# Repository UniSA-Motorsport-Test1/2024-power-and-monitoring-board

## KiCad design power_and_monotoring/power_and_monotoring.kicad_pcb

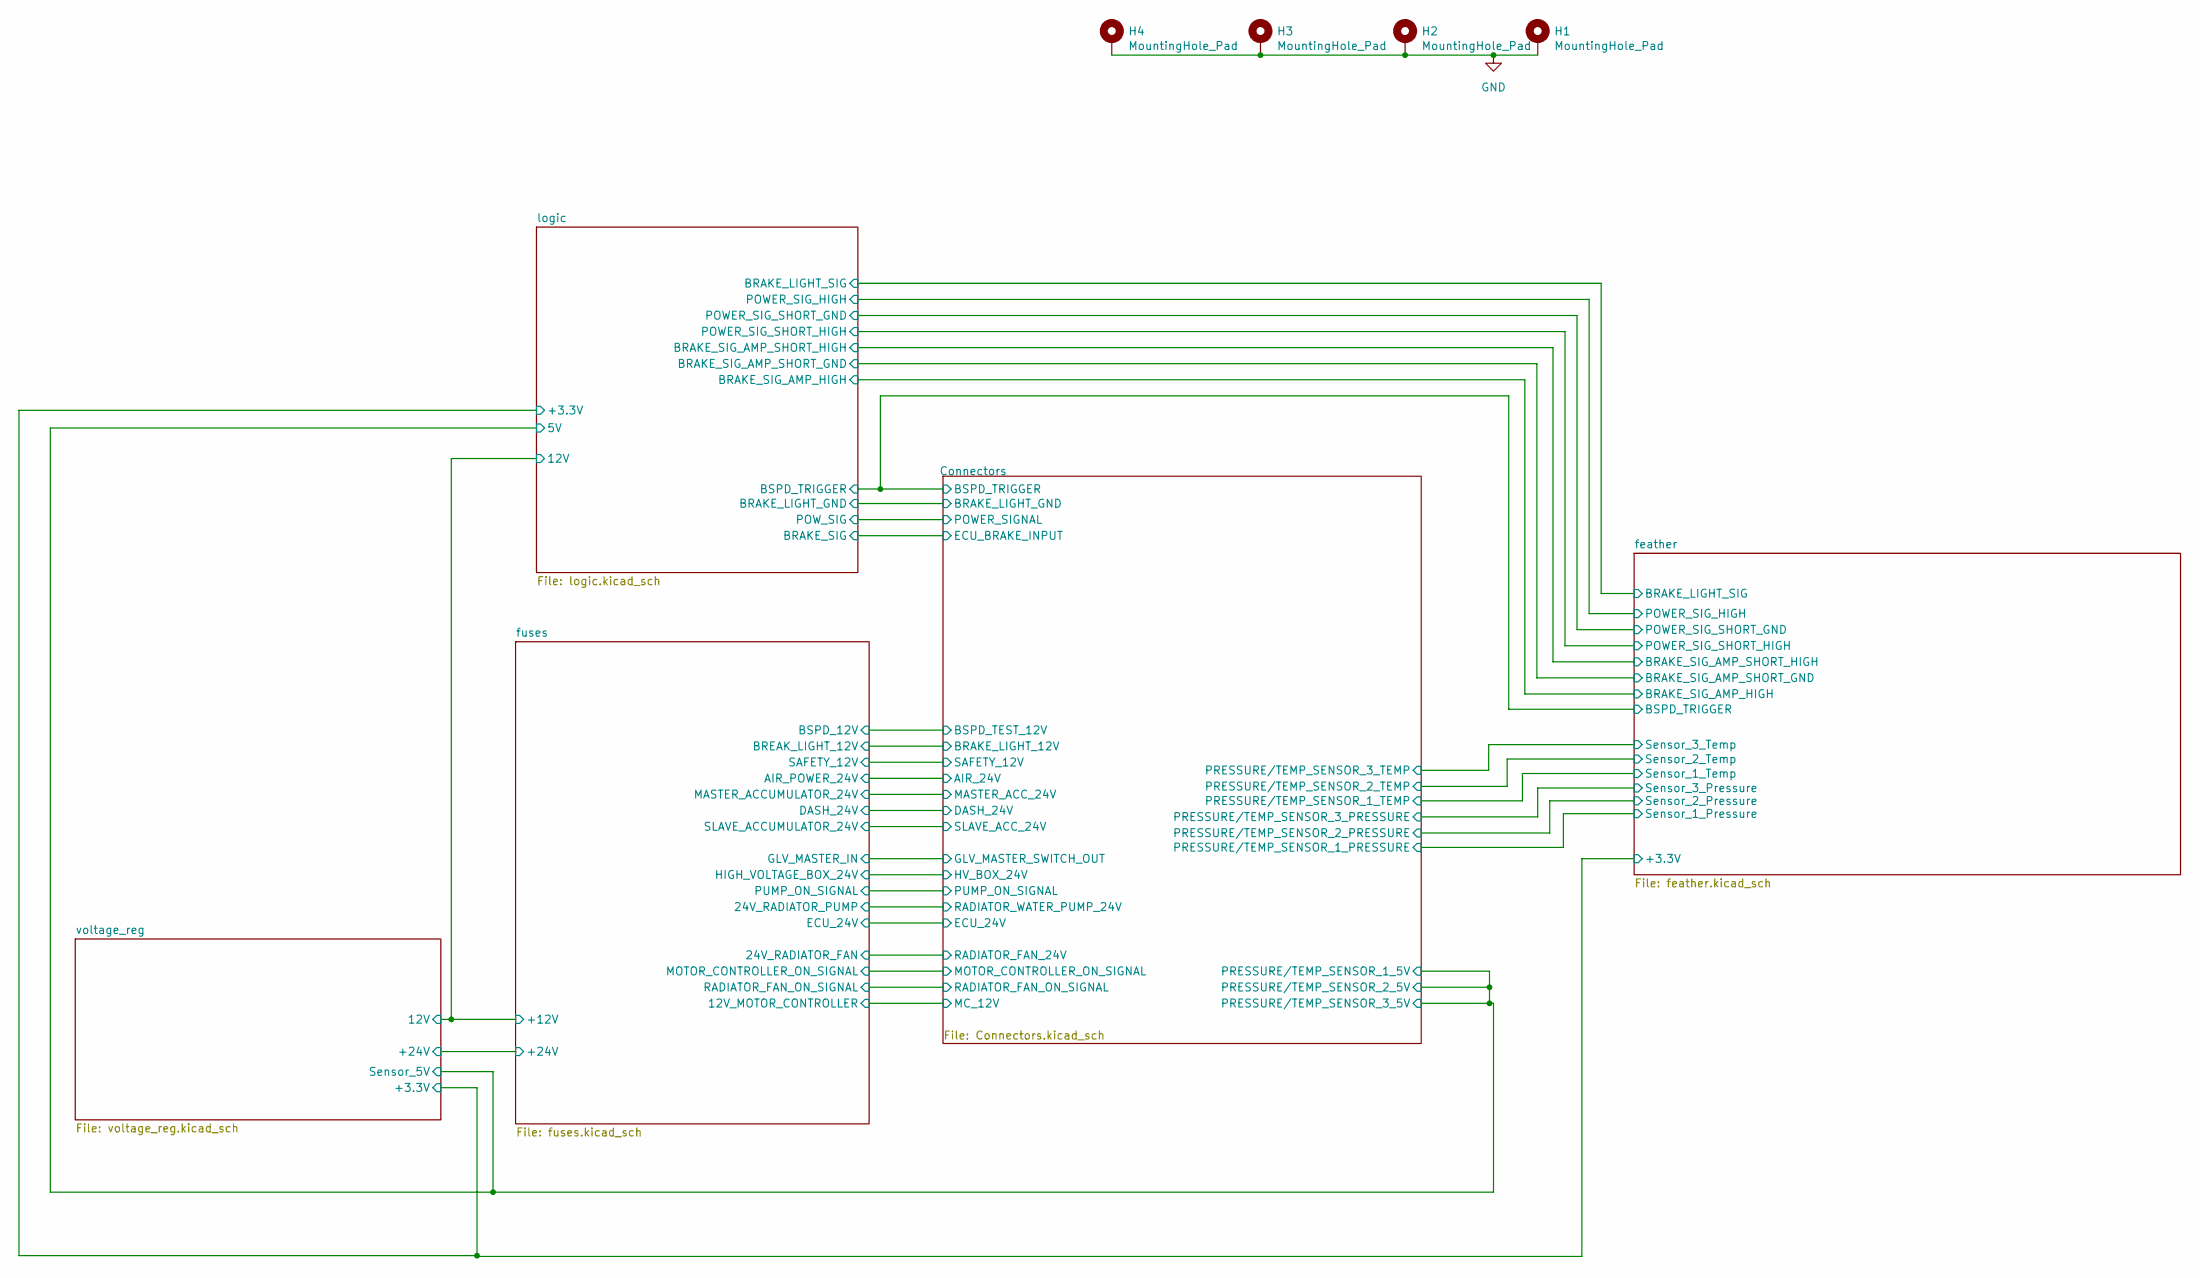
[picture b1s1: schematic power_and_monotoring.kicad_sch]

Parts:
H1, H2, H3, H4: MountingHole_Pad; MountingHole_3.2mm_M3_Pad_Via

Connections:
GND: H1.1, H2.1, H3.1, H4.1; also elsewhere on the board

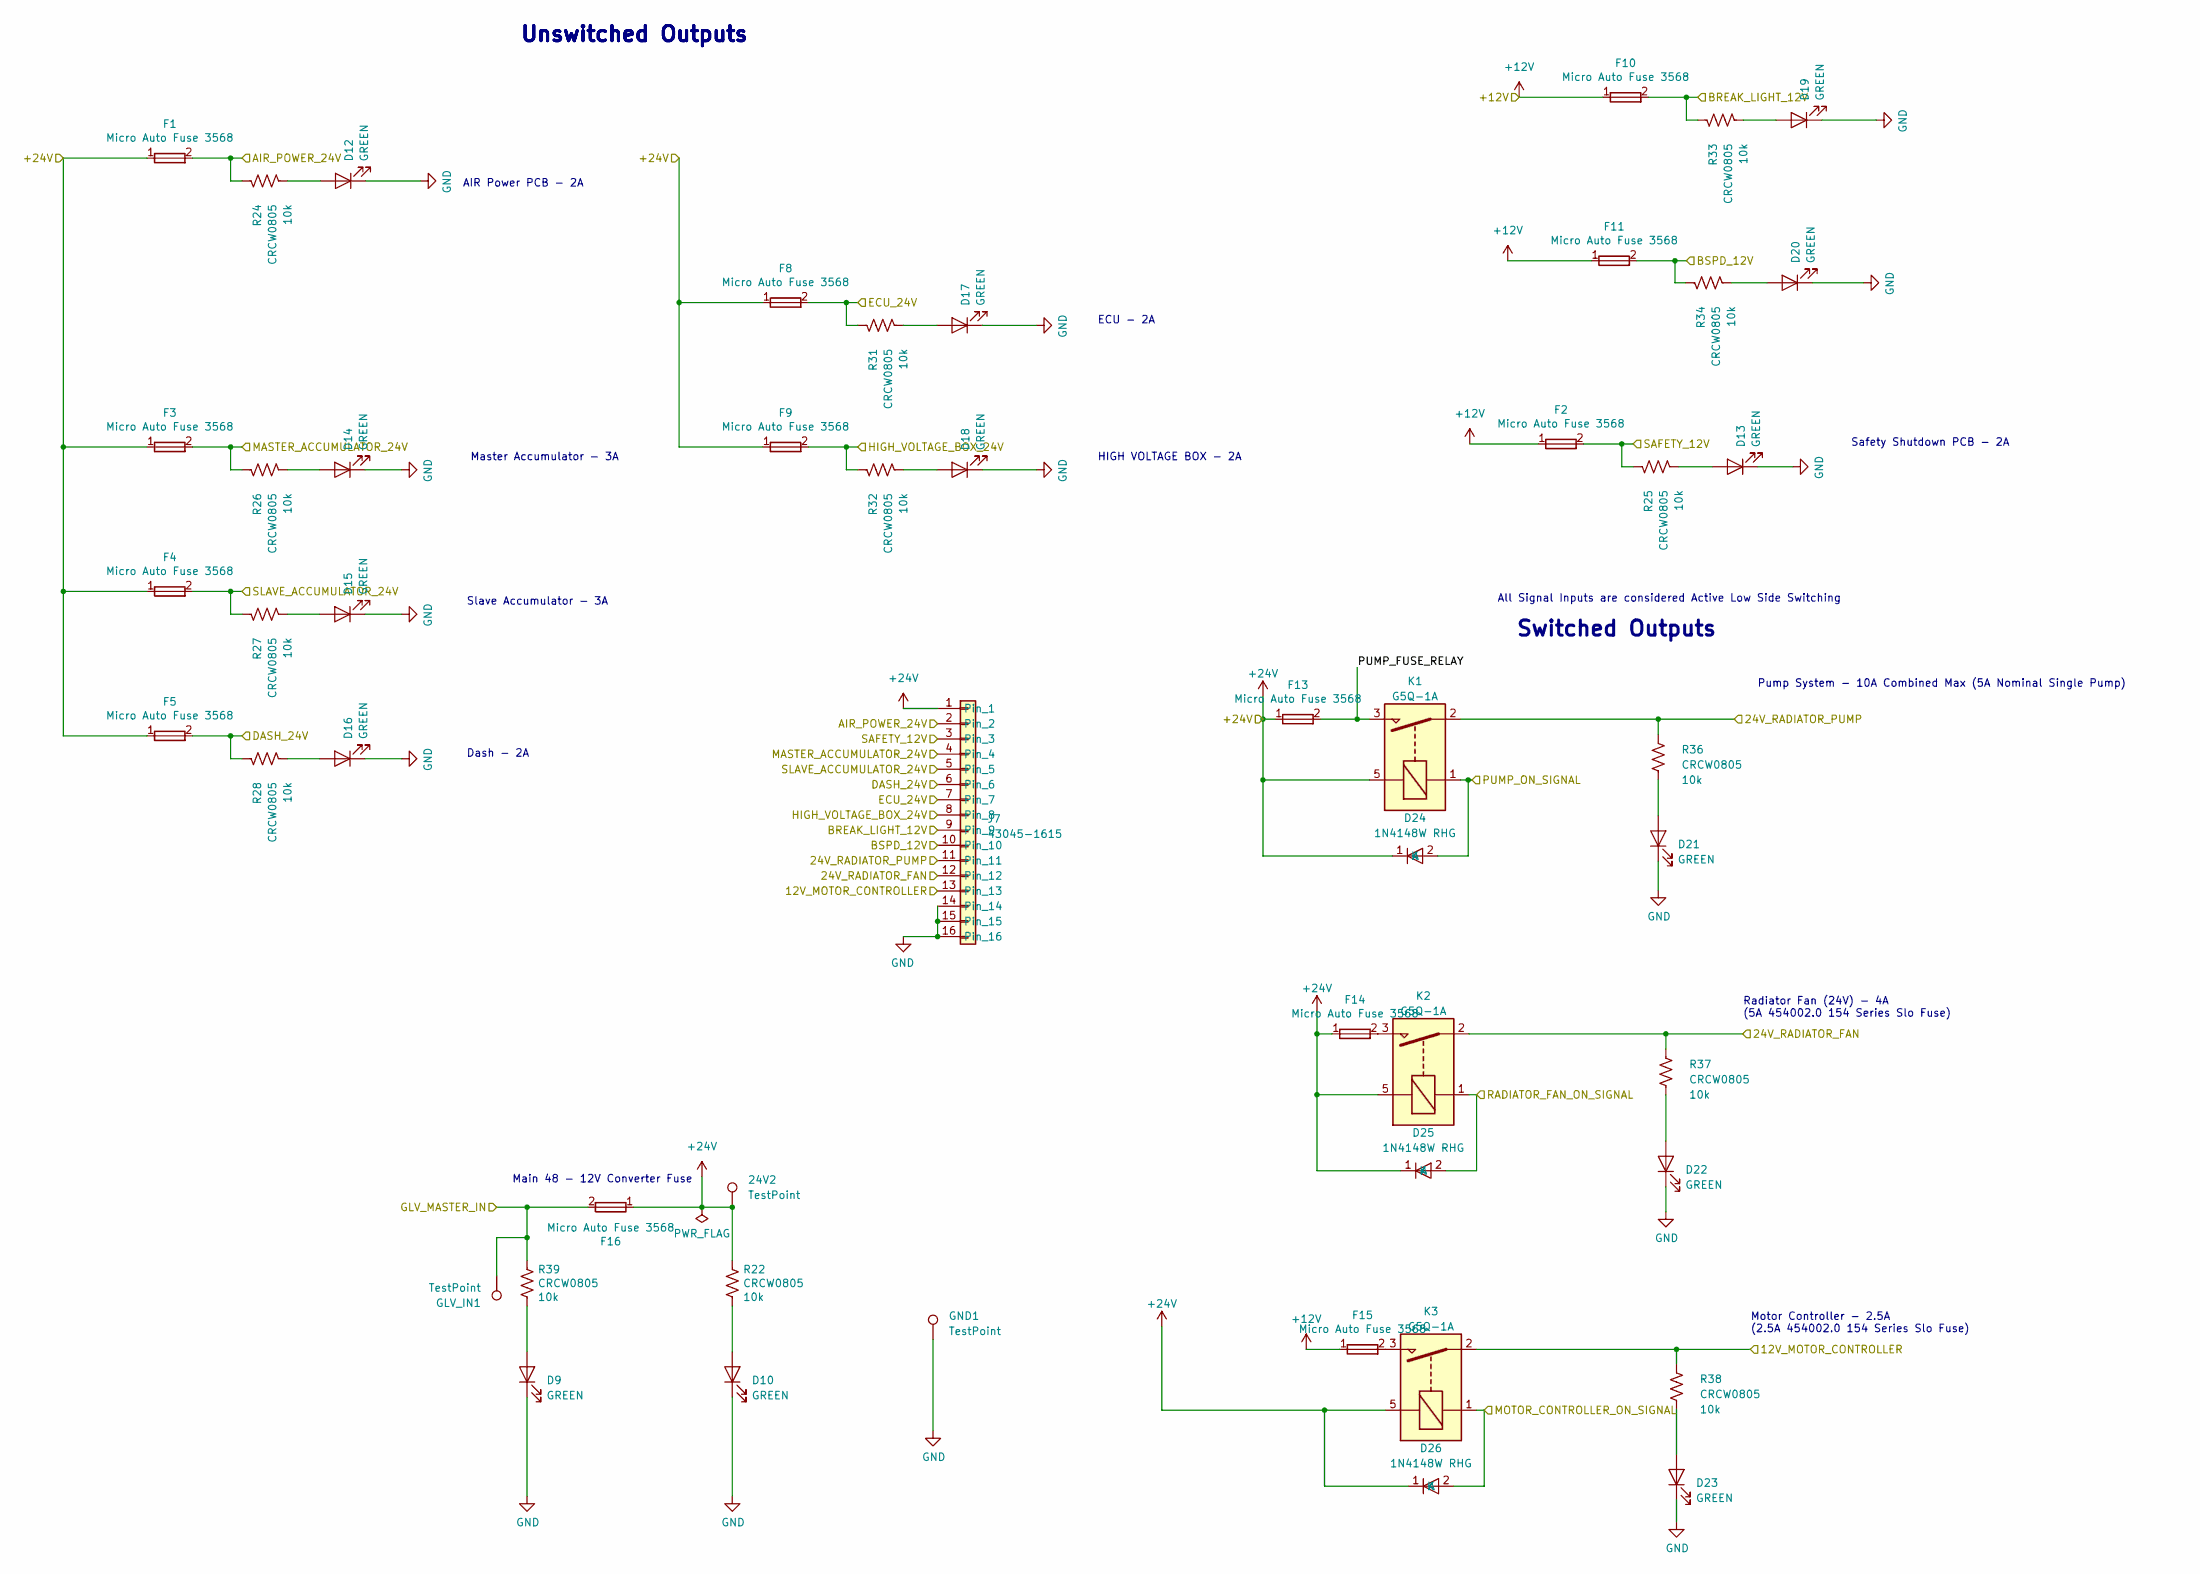
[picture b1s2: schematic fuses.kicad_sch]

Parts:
24V2: TestPoint; TestPoint_Pad_D2.0mm
D9, D10, D12, D13, D14, D15, D16, D17, D18, D19, D20, D21, D22, D23: GREEN; 0805
D24, D25, D26: 1N4148W RHG; SOD-123F-2
F1, F2, F3, F4, F5, F8, F9, F10, F11, F13, F14, F15, F16: Micro Auto Fuse 3568; Fuseholder_Blade_Mini_Keystone_3568; Voltage Rating 60V; Current Rating 10A
GLV_IN1: TestPoint; TestPoint_Pad_D2.0mm
GND1: TestPoint; TestPoint_Pad_D2.0mm
J7: 43045-1615; MOLEX_43045-16YY_16PIN
K1, K2, K3: G5Q-1A; Relay_SPST_Omron-G5Q-1A
R22, R24, R25, R26, R27, R28, R31, R32, R33, R34, R36, R37, R38, R39: CRCW0805; 0805; Voltage Rating 50V; Power Rating 63mW

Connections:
+12V: F2.1, F10.1, F11.1, F15.1; also elsewhere on the board
+24V: 24V2.1, D24.1 (K), D25.1 (K), D26.1 (K), F1.1, F3.1, F4.1, F5.1, F8.1, F9.1, F13.1, F14.1, F16.1, J7.1, K1.5, K2.5, K3.5, R22.1; also elsewhere on the board
/Connectors/AIR_24V: F1.2, J7.2, R24.1; also elsewhere on the board
/Connectors/BRAKE_LIGHT_12V: F10.2, J7.9, R33.1; also elsewhere on the board
/Connectors/BSPD_TEST_12V: F11.2, J7.10, R34.1; also elsewhere on the board
/Connectors/DASH_24V: F5.2, J7.6, R28.1; also elsewhere on the board
/Connectors/ECU_24V: F8.2, J7.7, R31.1; also elsewhere on the board
/Connectors/GLV_MASTER_SWITCH_OUT: F16.2, GLV_IN1.1, R39.1; also elsewhere on the board
/Connectors/HV_BOX_24V: F9.2, J7.8, R32.1; also elsewhere on the board
/Connectors/MASTER_ACC_24V: F3.2, J7.4, R26.1; also elsewhere on the board
/Connectors/MC_12V: J7.13, K3.2, R38.1; also elsewhere on the board
/Connectors/MOTOR_CONTROLLER_ON_SIGNAL: D26.2 (A), K3.1; also elsewhere on the board
/Connectors/PUMP_ON_SIGNAL: D24.2 (A), K1.1; also elsewhere on the board
/Connectors/RADIATOR_FAN_24V: J7.12, K2.2, R37.1; also elsewhere on the board
/Connectors/RADIATOR_FAN_ON_SIGNAL: D25.2 (A), K2.1; also elsewhere on the board
/Connectors/RADIATOR_WATER_PUMP_24V: J7.11, K1.2, R36.1; also elsewhere on the board
/Connectors/SAFETY_24V: F2.2, J7.3, R25.1; also elsewhere on the board
/Connectors/SLAVE_ACC_24V: F4.2, J7.5, R27.1; also elsewhere on the board
/fuses/PUMP_FUSE_RELAY: F13.2, K1.3
GND: D9.1 (K), D10.1 (K), D12.1 (K), D13.1 (K), D14.1 (K), D15.1 (K), D16.1 (K), D17.1 (K), D18.1 (K), D19.1 (K), D20.1 (K), D21.1 (K), D22.1 (K), D23.1 (K), GND1.1, J7.14, J7.15, J7.16; also elsewhere on the board
unnamed: D9.2 (A), R39.2
unnamed: D10.2 (A), R22.2
unnamed: D12.2 (A), R24.2
unnamed: D13.2 (A), R25.2
unnamed: D14.2 (A), R26.2
unnamed: D15.2 (A), R27.2
unnamed: D16.2 (A), R28.2
unnamed: D17.2 (A), R31.2
unnamed: D18.2 (A), R32.2
unnamed: D19.2 (A), R33.2
unnamed: D20.2 (A), R34.2
unnamed: D21.2 (A), R36.2
unnamed: D22.2 (A), R37.2
unnamed: D23.2 (A), R38.2
unnamed: F14.2, K2.3
unnamed: F15.2, K3.3

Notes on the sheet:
ECU - 2A
Motor Controller - 2.5A (2.5A 454002.0 154 Series Slo Fuse)
Unswitched Outputs
AIR Power PCB - 2A
Safety Shutdown PCB - 2A
All Signal Inputs are considered Active Low Side Switching
HIGH VOLTAGE BOX - 2A
Radiator Fan (24V) - 4A (5A 454002.0 154 Series Slo Fuse)
Main 48 - 12V Converter Fuse
Dash - 2A
Master Accumulator - 3A
Switched Outputs
Pump System - 10A Combined Max (5A Nominal Single Pump)
Slave Accumulator - 3A

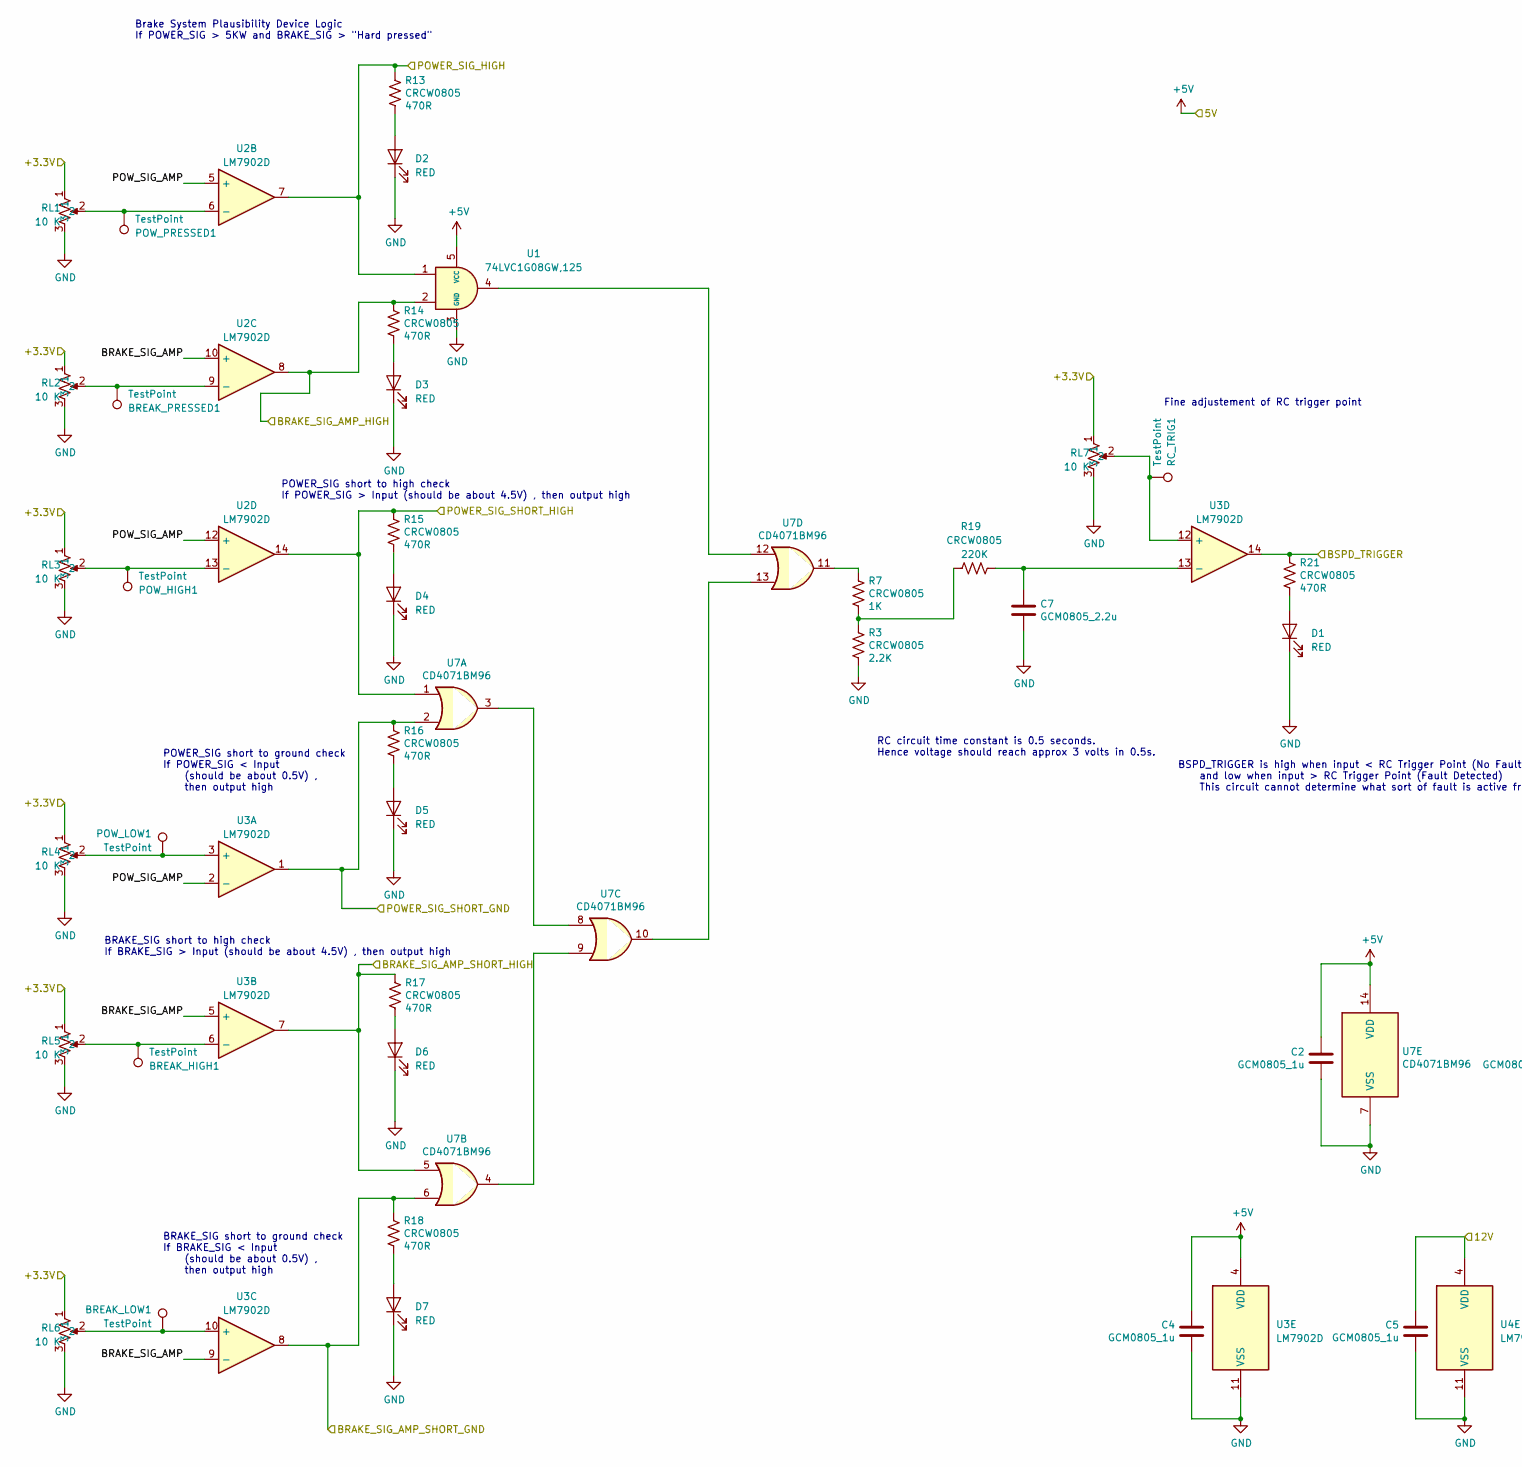
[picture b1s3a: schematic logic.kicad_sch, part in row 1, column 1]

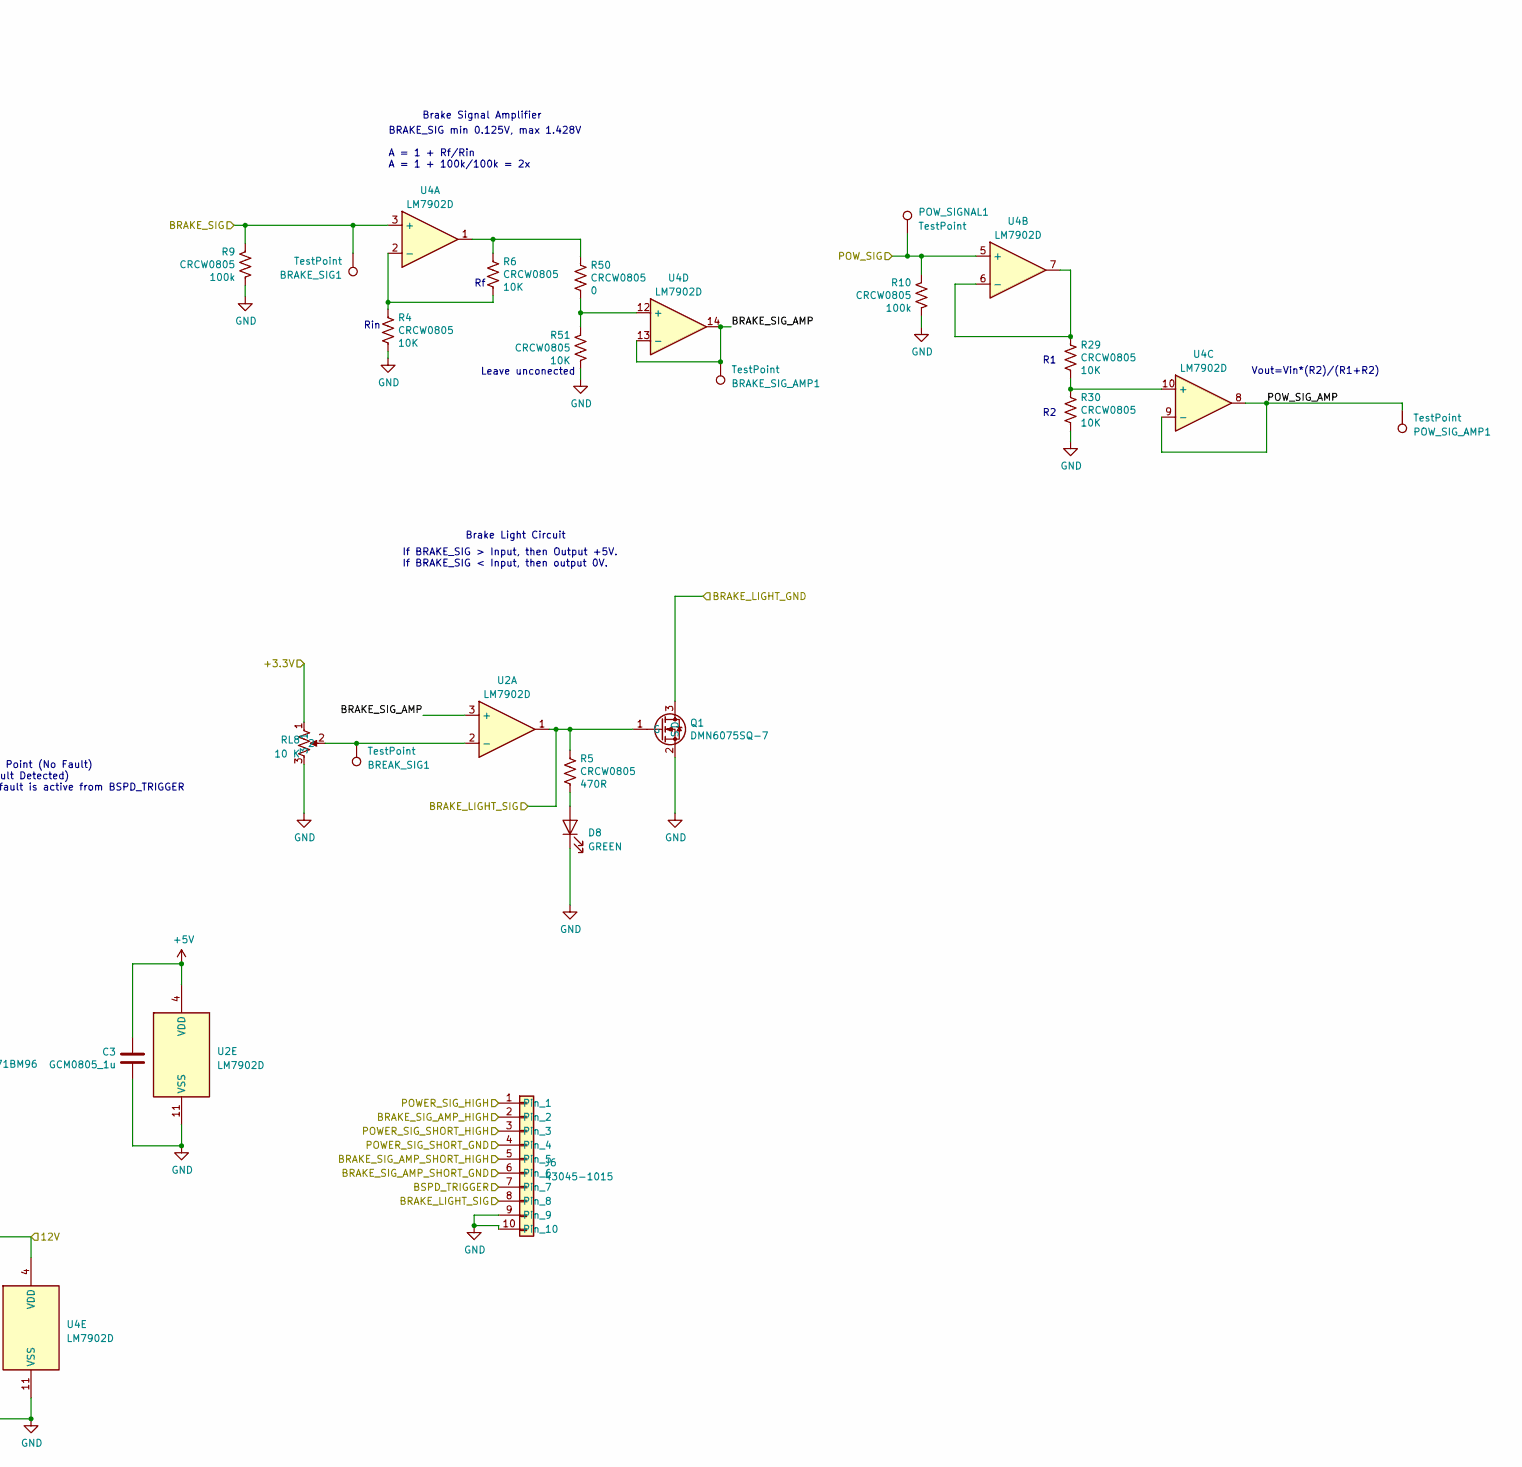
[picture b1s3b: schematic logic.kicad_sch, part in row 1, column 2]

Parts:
BRAKE_SIG1: TestPoint; TestPoint_Pad_D2.0mm
BRAKE_SIG_AMP1: TestPoint; TestPoint_Pad_D2.0mm
BREAK_HIGH1: TestPoint; TestPoint_Pad_D2.0mm
BREAK_LOW1: TestPoint; TestPoint_Pad_D2.0mm
BREAK_PRESSED1: TestPoint; TestPoint_Pad_D2.0mm
BREAK_SIG1: TestPoint; TestPoint_Pad_D2.0mm
C2, C3, C4, C5: GCM0805_1u; 0805; Voltage Rating 50V
C7: GCM0805_2.2u; 0805; Voltage Rating 16V
D1, D2, D3, D4, D5, D6, D7: RED; 0805
D8: GREEN; 0805
J6: 43045-1015; MOLEX_43045-10YY_10PIN
POW_HIGH1: TestPoint; TestPoint_Pad_D2.0mm
POW_LOW1: TestPoint; TestPoint_Pad_D2.0mm
POW_PRESSED1: TestPoint; TestPoint_Pad_D2.0mm
POW_SIGNAL1: TestPoint; TestPoint_Pad_D2.0mm
POW_SIG_AMP1: TestPoint; TestPoint_Pad_D2.0mm
Q1: DMN6075SQ-7; SOT-23-3
R3, R4, R5, R6, R7, R9, R10, R13, R14, R15, R16, R17, R18, R19, R21, R29, R30, R50, R51: CRCW0805; 0805; Voltage Rating 150V; Power Rating 125mW
RC_TRIG1: TestPoint; TestPoint_Pad_D2.0mm
RL1, RL2, RL3, RL4, RL5, RL6, RL7, RL8: 10 K; 3296W-1
U1: 74LVC1G08GW,125; TSSOP-5
U2, U3, U4: LM7902D; SOIC-14
U7: CD4071BM96; SOIC-14

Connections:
+3V3: RL1.1, RL2.1, RL3.1, RL4.1, RL5.1, RL6.1, RL7.1, RL8.1; also elsewhere on the board
+5V: C2.1, C3.1, C4.1, U1.5 (VCC), U2.4 (VDD), U3.4 (VDD), U7.14 (VDD); also elsewhere on the board
+12V: C5.1, U4.4 (VDD); also elsewhere on the board
/Connectors/BRAKE_LIGHT_GND: Q1.3 (D); also elsewhere on the board
/Connectors/BSPD_TRIGGER: J6.7, R21.1, U3.14; also elsewhere on the board
/Connectors/ECU_BRAKE_INPUT: BRAKE_SIG1.1, R9.1, U4.3 (+); also elsewhere on the board
/Connectors/POWER_SIGNAL: POW_SIGNAL1.1, R10.1, U4.5 (+); also elsewhere on the board
/feather/BRAKE_LIGHT_SIG: J6.8, Q1.1 (G), R5.1, U2.1; also elsewhere on the board
/feather/BRAKE_SIG_AMP_HIGH: J6.2, R14.1, U1.2, U2.8; also elsewhere on the board
/feather/BRAKE_SIG_AMP_SHORT_GND: J6.6, R18.1, U3.8, U7.6; also elsewhere on the board
/feather/BRAKE_SIG_AMP_SHORT_HIGH: J6.5, R17.1, U3.7, U7.5; also elsewhere on the board
/feather/POWER_SIG_HIGH: J6.1, R13.1, U1.1, U2.7; also elsewhere on the board
/feather/POWER_SIG_SHORT_GND: J6.4, R16.1, U3.1, U7.2; also elsewhere on the board
/feather/POWER_SIG_SHORT_HIGH: J6.3, R15.1, U2.14, U7.1; also elsewhere on the board
/logic/BRAKE_SIG_AMP: BRAKE_SIG_AMP1.1, U2.3 (+), U2.10 (+), U3.5 (+), U3.9 (-), U4.13 (-), U4.14
/logic/POW_SIG_AMP: POW_SIG_AMP1.1, U2.5 (+), U2.12 (+), U3.2 (-), U4.8, U4.9 (-)
GND: C2.2, C3.2, C4.2, C5.2, C7.2, D1.1 (K), D2.1 (K), D3.1 (K), D4.1 (K), D5.1 (K), D6.1 (K), D7.1 (K), D8.1 (K), J6.9, J6.10, Q1.2 (S), R3.2, R4.2, R9.2, R10.2, R30.2, R51.2, RL1.3, RL2.3, RL3.3, RL4.3, RL5.3, RL6.3, RL7.3, RL8.3, U1.3 (GND), U2.11 (VSS), U3.11 (VSS), U4.11 (VSS), U7.7 (VSS); also elsewhere on the board
unnamed: D1.2 (A), R21.2
unnamed: D2.2 (A), R13.2
unnamed: D3.2 (A), R14.2
unnamed: D4.2 (A), R15.2
unnamed: D5.2 (A), R16.2
unnamed: D6.2 (A), R17.2
unnamed: D7.2 (A), R18.2
unnamed: D8.2 (A), R5.2
unnamed: R7.1, U7.11
unnamed: R3.1, R7.2, R19.1
unnamed: R6.1, R50.1, U4.1
unnamed: U1.4, U7.12
unnamed: BREAK_SIG1.1, RL8.2, U2.2 (-)
unnamed: POW_PRESSED1.1, RL1.2, U2.6 (-)
unnamed: BREAK_PRESSED1.1, RL2.2, U2.9 (-)
unnamed: POW_HIGH1.1, RL3.2, U2.13 (-)
unnamed: POW_LOW1.1, RL4.2, U3.3 (+)
unnamed: BREAK_HIGH1.1, RL5.2, U3.6 (-)
unnamed: BREAK_LOW1.1, RL6.2, U3.10 (+)
unnamed: RC_TRIG1.1, RL7.2, U3.12 (+)
unnamed: C7.1, R19.2, U3.13 (-)
unnamed: R4.1, R6.2, U4.2 (-)
unnamed: R29.1, U4.6 (-), U4.7
unnamed: R29.2, R30.1, U4.10 (+)
unnamed: R50.2, R51.1, U4.12 (+)
unnamed: U7.3, U7.8
unnamed: U7.4, U7.9
unnamed: U7.10, U7.13

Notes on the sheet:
If BRAKE_SIG > Input, then Output +5V. If BRAKE_SIG < Input, then output 0V.
POWER_SIG short to high check If POWER_SIG > Input (should be about 4.5V) , then output high
Leave unconected
POWER_SIG short to ground check If POWER_SIG < Input (should be about 0.5V) , then output high
RC circuit time constant is 0.5 seconds. Hence voltage should reach approx 3 volts in 0.5s.
Brake System Plausibility Device Logic If POWER_SIG > 5KW and BRAKE_SIG > "Hard pressed"
Brake Light Circuit
Vout=Vin*(R2)/(R1+R2)
BRAKE_SIG short to ground check If BRAKE_SIG < Input (should be about 0.5V) , then output high
Rin
BRAKE_SIG short to high check If BRAKE_SIG > Input (should be about 4.5V) , then output high
Fine adjustement of RC trigger point
Brake Signal Amplifier
BRAKE_SIG min 0.125V, max 1.428V A = 1 + Rf/Rin A = 1 + 100k/100k = 2x
BSPD_TRIGGER is high when input < RC Trigger Point (No Fault) and low when input > RC Trigger Point (Fault Detected) This circuit cannot determine what sort of fault is active from BSPD_TRIGGER

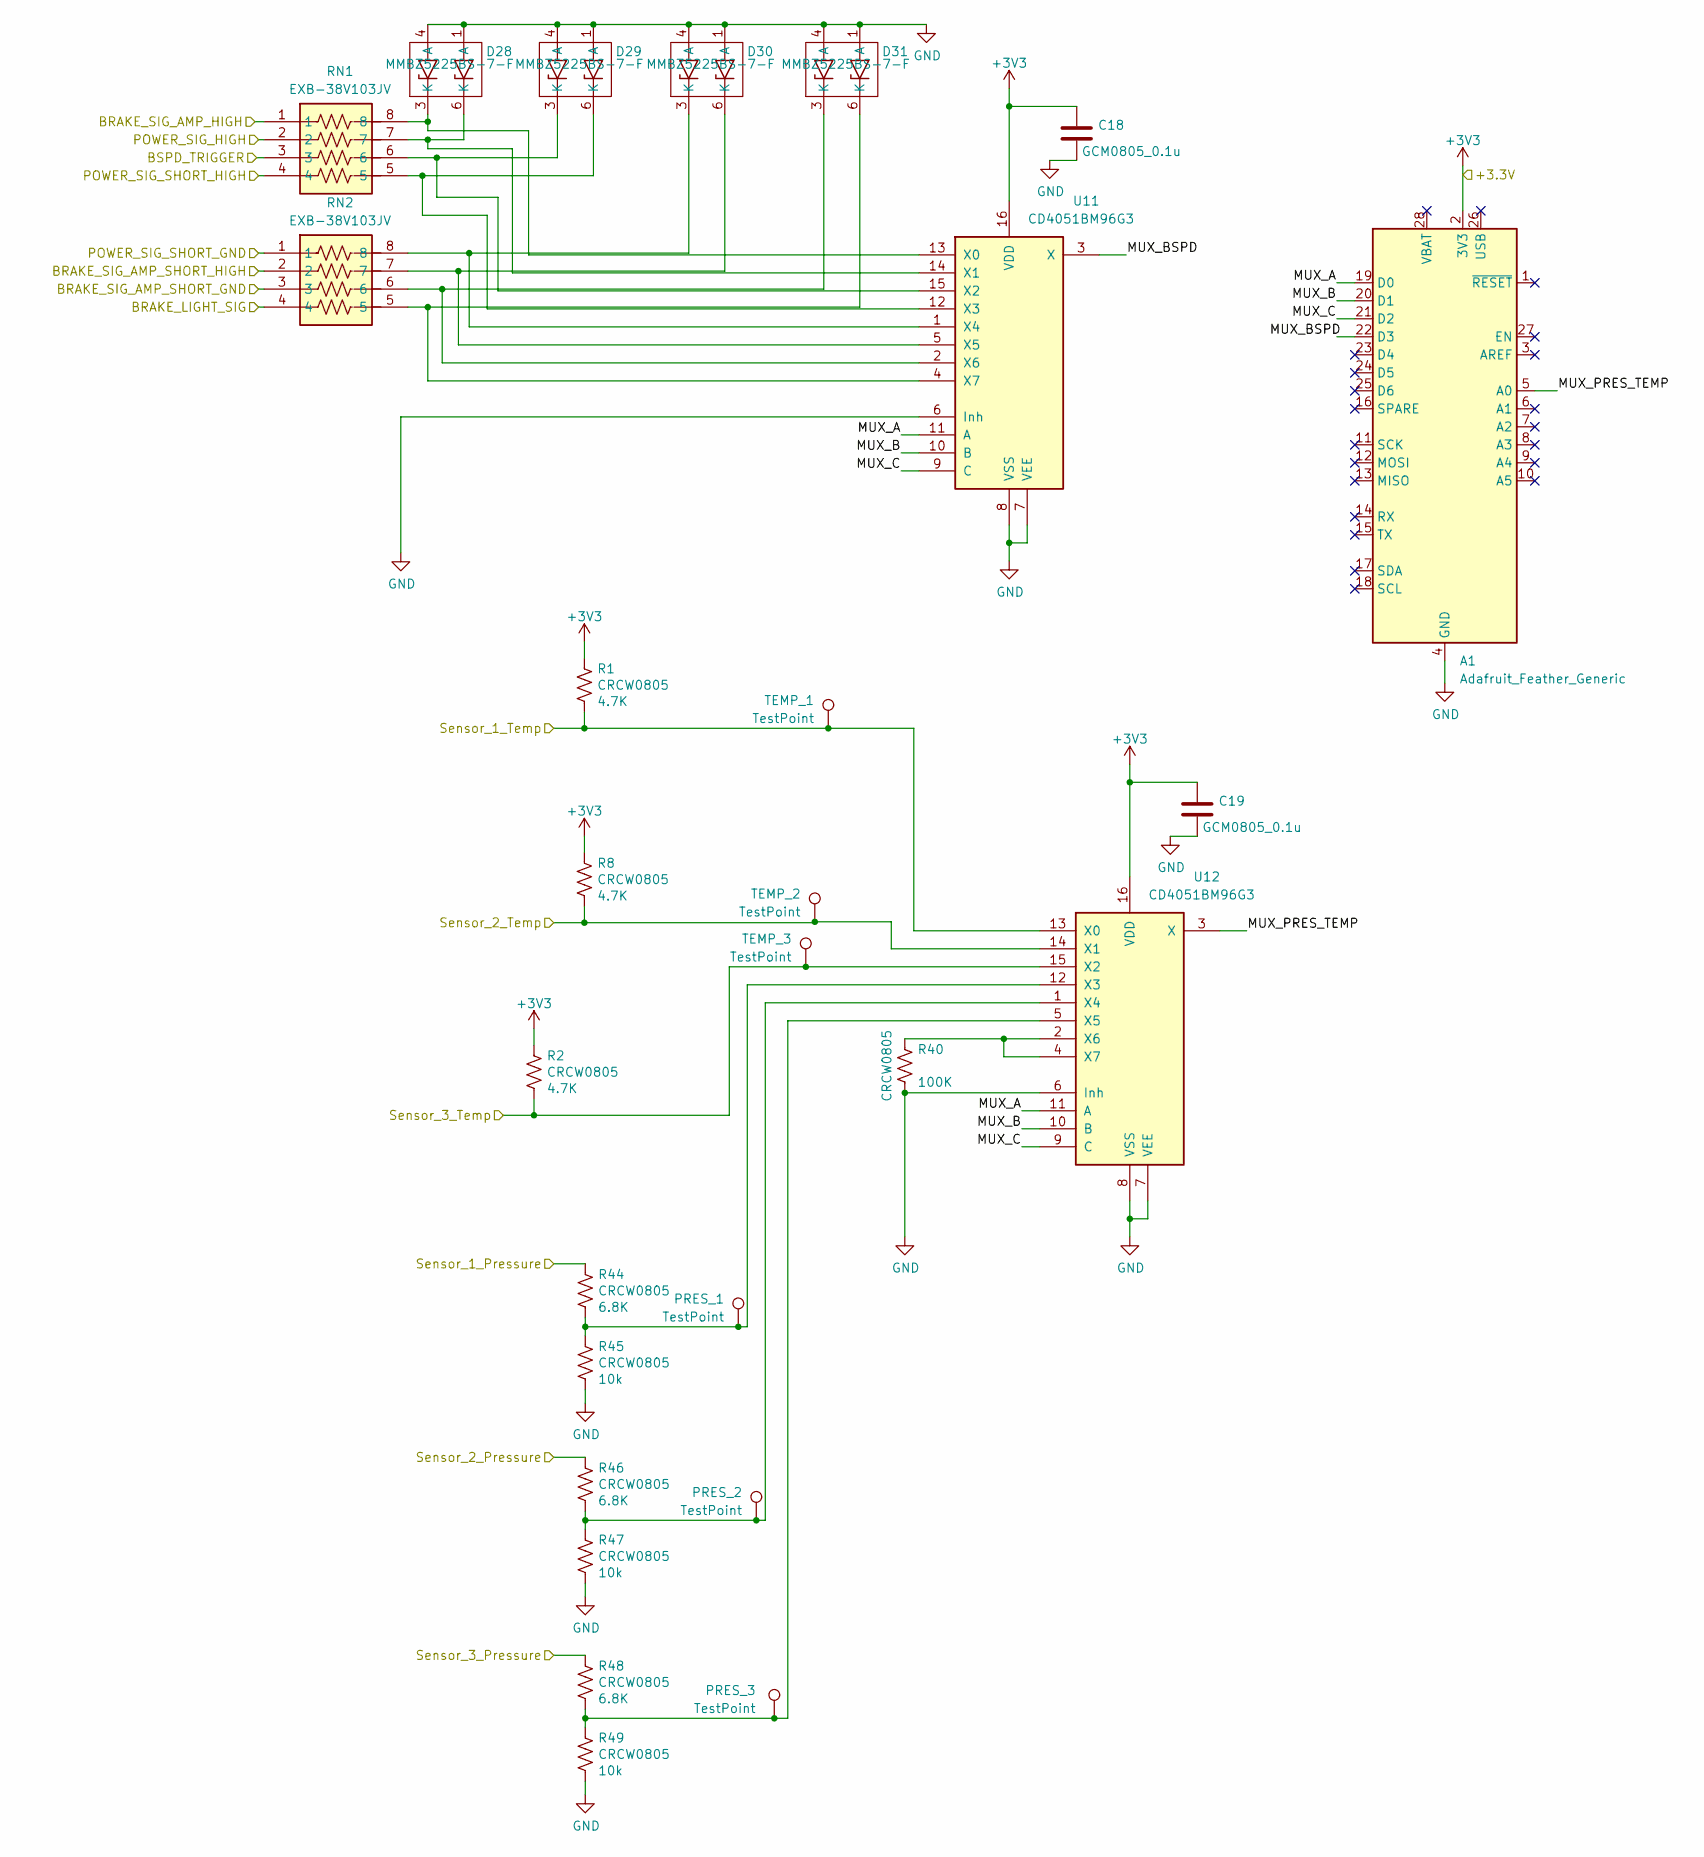
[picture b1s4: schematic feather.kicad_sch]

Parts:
A1: Adafruit_Feather_Generic; Adafruit_Feather_WithMountingHoles
C18, C19: GCM0805_0.1u; 0805; Voltage Rating 16V
D28, D29, D30, D31: MMBZ5225BS-7-F; SOT-363
PRES_1, PRES_2, PRES_3: TestPoint; TestPoint_Pad_D2.0mm
R1, R2, R8, R40, R44, R45, R46, R47, R48, R49: CRCW0805; 0805; Voltage Rating 150V; Power Rating 125mW
RN1, RN2: EXB-38V103JV; EXB38V472JV; Mouser Part Number 667-EXB-38V103JV
TEMP_1, TEMP_2, TEMP_3: TestPoint; TestPoint_Pad_D2.0mm
U11, U12: CD4051BM96G3; SOIC-16

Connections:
+3V3: A1.2 (3V3), C18.1, C19.1, R1.1, R2.1, R8.1, U11.16 (VDD), U12.16 (VDD); also elsewhere on the board
/Connectors/BSPD_TRIGGER: RN1.3; also elsewhere on the board
/Connectors/PRESSURE/TEMP_SENSOR_1_PRESSURE: R44.1; also elsewhere on the board
/Connectors/PRESSURE/TEMP_SENSOR_1_TEMP: R1.2, TEMP_1.1, U12.13 (X0); also elsewhere on the board
/Connectors/PRESSURE/TEMP_SENSOR_2_PRESSURE: R46.1; also elsewhere on the board
/Connectors/PRESSURE/TEMP_SENSOR_2_TEMP: R8.2, TEMP_2.1, U12.14 (X1); also elsewhere on the board
/Connectors/PRESSURE/TEMP_SENSOR_3_PRESSURE: R48.1; also elsewhere on the board
/Connectors/PRESSURE/TEMP_SENSOR_3_TEMP: R2.2, TEMP_3.1, U12.15 (X2); also elsewhere on the board
/feather/BRAKE_LIGHT_SIG: RN2.4; also elsewhere on the board
/feather/BRAKE_SIG_AMP_HIGH: RN1.1; also elsewhere on the board
/feather/BRAKE_SIG_AMP_SHORT_GND: RN2.3; also elsewhere on the board
/feather/BRAKE_SIG_AMP_SHORT_HIGH: RN2.2; also elsewhere on the board
/feather/MUX_A: A1.19 (D0), U11.11 (A), U12.11 (A)
/feather/MUX_B: A1.20 (D1), U11.10 (B), U12.10 (B)
/feather/MUX_BSPD: A1.22 (D3), U11.3 (X)
/feather/MUX_C: A1.21 (D2), U11.9 (C), U12.9 (C)
/feather/MUX_PRES_TEMP: A1.5 (A0), U12.3 (X)
/feather/POWER_SIG_HIGH: RN1.2; also elsewhere on the board
/feather/POWER_SIG_SHORT_GND: RN2.1; also elsewhere on the board
/feather/POWER_SIG_SHORT_HIGH: RN1.4; also elsewhere on the board
GND: A1.4 (GND), C18.2, C19.2, D28.1 (A), D28.4 (A), D29.1 (A), D29.4 (A), D30.1 (A), D30.4 (A), D31.1 (A), D31.4 (A), R40.2, R45.2, R47.2, R49.2, U11.6 (Inh), U11.7 (VEE), U11.8 (VSS), U12.6 (Inh), U12.7 (VEE), U12.8 (VSS); also elsewhere on the board
unnamed: D28.3 (K), RN1.8, U11.13 (X0)
unnamed: D28.6 (K), RN1.7, U11.14 (X1)
unnamed: D29.3 (K), RN1.6, U11.15 (X2)
unnamed: D29.6 (K), RN1.5, U11.12 (X3)
unnamed: D30.3 (K), RN2.8, U11.1 (X4)
unnamed: D30.6 (K), RN2.7, U11.5 (X5)
unnamed: D31.3 (K), RN2.6, U11.2 (X6)
unnamed: D31.6 (K), RN2.5, U11.4 (X7)
unnamed: PRES_1.1, R44.2, R45.1, U12.12 (X3)
unnamed: PRES_2.1, R46.2, R47.1, U12.1 (X4)
unnamed: PRES_3.1, R48.2, R49.1, U12.5 (X5)
unnamed: R40.1, U12.2 (X6), U12.4 (X7)
